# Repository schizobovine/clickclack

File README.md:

# clickclack
Clicky clacky keyboard thingy.

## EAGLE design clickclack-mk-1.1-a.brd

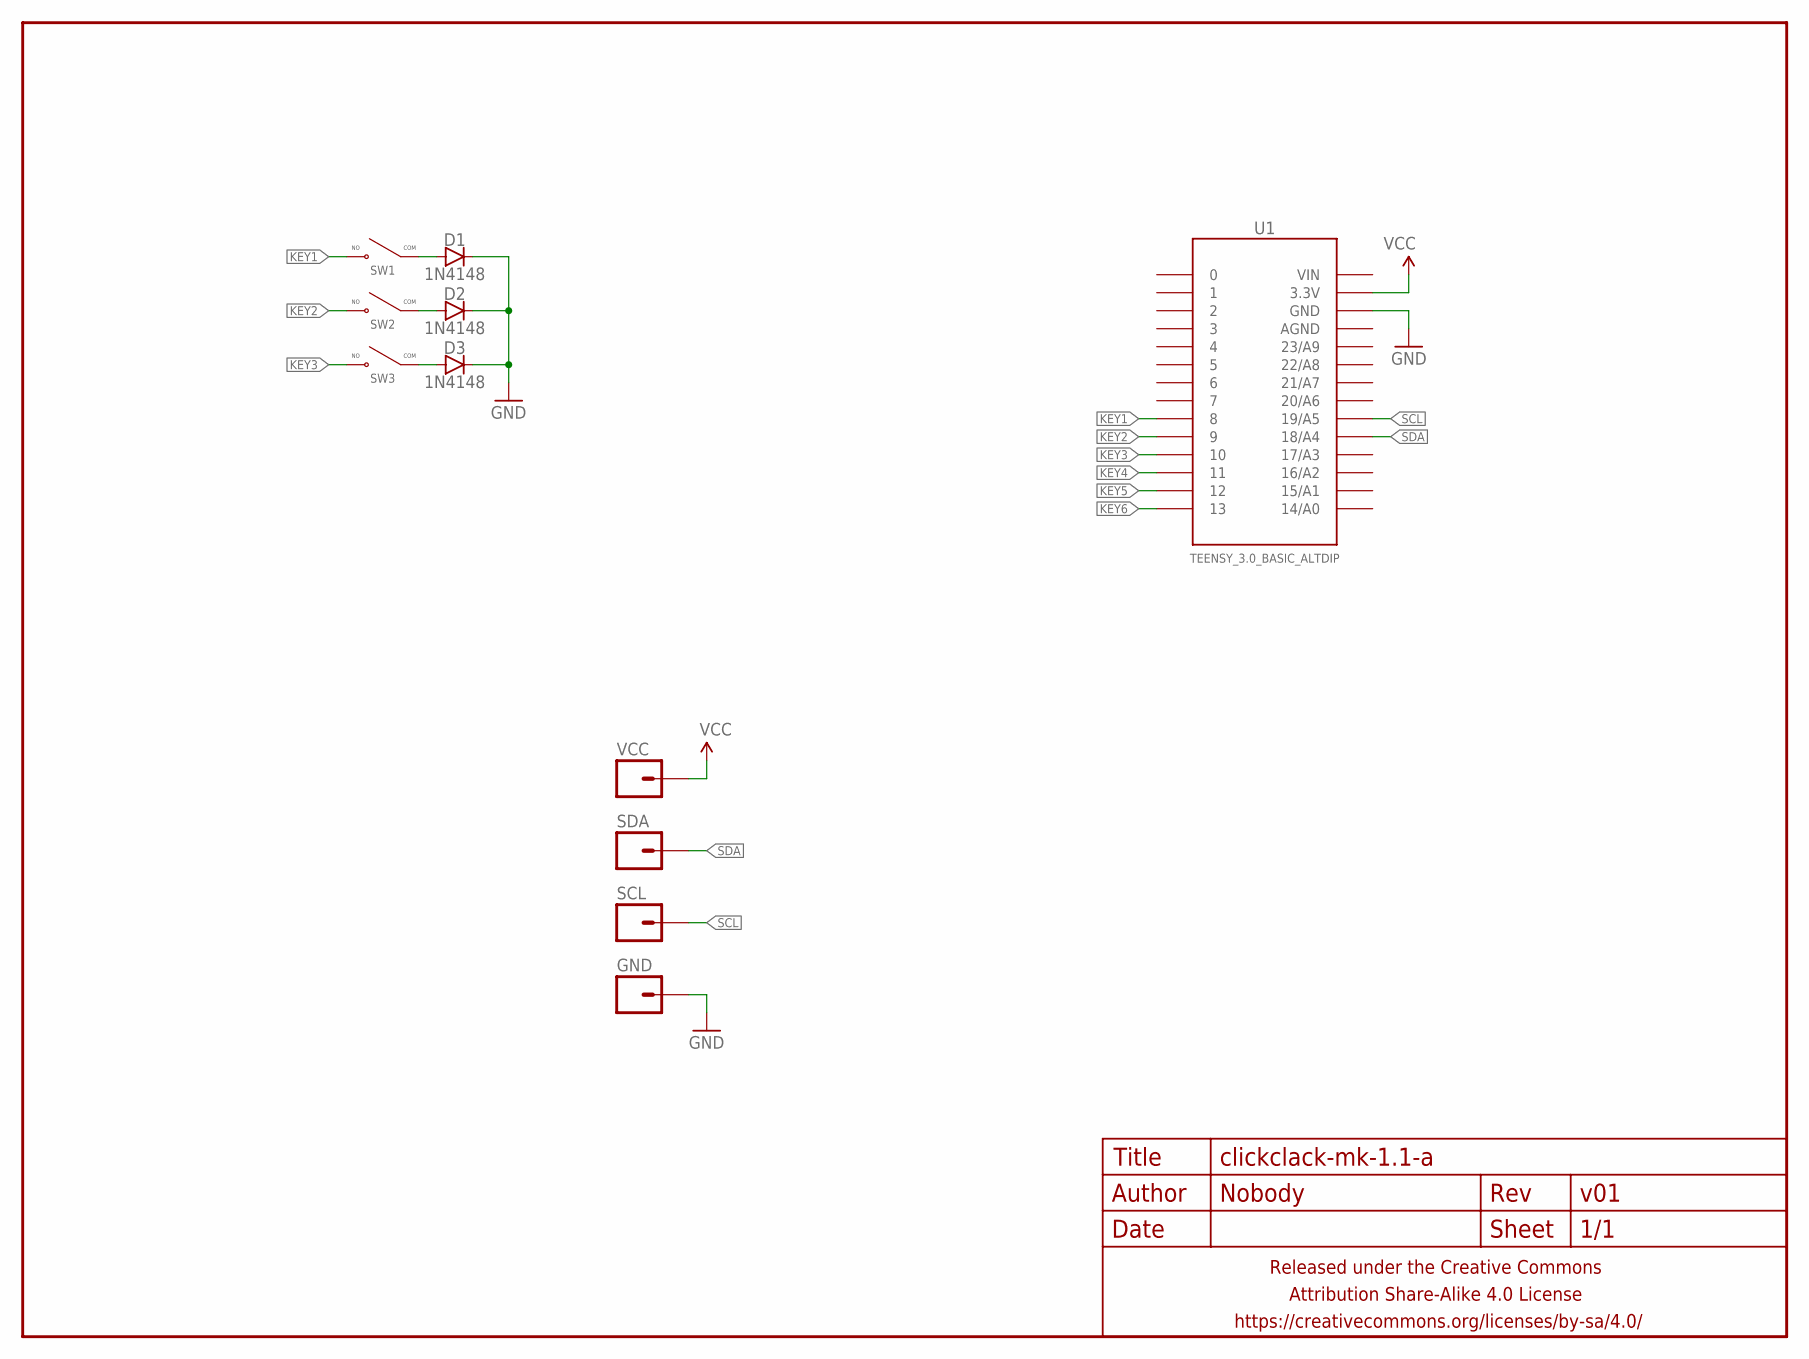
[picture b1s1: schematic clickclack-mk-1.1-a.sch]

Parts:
D1, D2, D3: 1N4148; DIODE-7.62MM
FRAME1: FRAME-LETTERNO_PACKAGE; DUMMY
GND: M01PTH; 1X01
SCL: M01PTH; 1X01
SDA: M01PTH; 1X01
SW1, SW2, SW3: CHERRY-MXNONUBS; CHERRY-MX-NONUBS
U1: TEENSY_3.0_BASIC_ALTDIP; TEENSY_3.0_BASIC_ALT2
VCC: M01PTH; 1X01

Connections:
AGND: U1.AGND
GND: D1.K (C), D2.K (C), D3.K (C), GND.1, U1.GND
KEY1: SW1.2 (NO), U1.8
KEY2: SW2.2 (NO), U1.9
KEY3: SW3.2 (NO), U1.10
KEY4: U1.11
KEY5: U1.12
KEY6: U1.13
unnamed: D1.A, SW1.1 (COM)
unnamed: D2.A, SW2.1 (COM)
unnamed: D3.A, SW3.1 (COM)
SCL: SCL.1, U1.19/A5
SDA: SDA.1, U1.18/A4
VCC: U1.3.3V, VCC.1
VIN: U1.VIN

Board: 2 copper layers, 12 parts (4 on the bottom side), 10 nets, no tracks yet.

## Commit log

2015-10-09 various renderings in PDF
2015-10-09 added dimensions to board
2015-10-09 png renderings from oshpark
2015-10-19 spliting board into two parts
2015-10-21 [wip] do not use

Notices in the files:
parts and their libraries:
A_butts: Released under the Creative Commons Attribution Share-Alike 4.0 License
A_butts: https://creativecommons.org/licenses/by-sa/4.0
A_butts: Released under the Creative Commons
